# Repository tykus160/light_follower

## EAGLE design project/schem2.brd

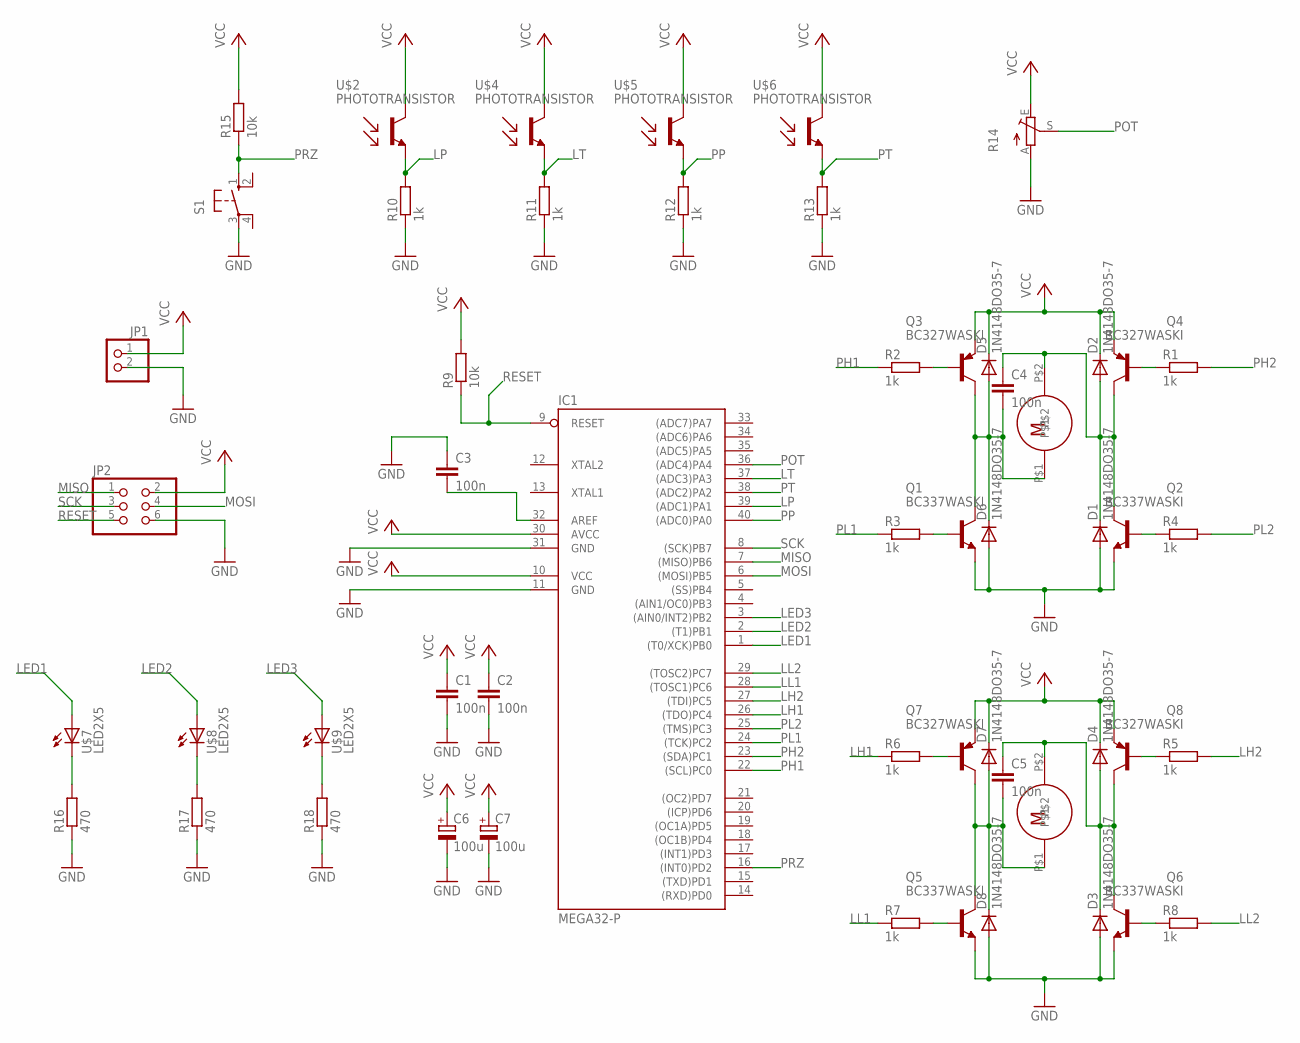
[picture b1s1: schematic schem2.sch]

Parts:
C1, C2, C3, C4, C5: 100n; C025-025X050
C6, C7: 100u; E2-5
D1, D2, D3, D4, D5, D6, D7, D8: 1N4148DO35-7; DO35-7
IC1: MEGA32-P; DIL40
JP1: PINHD-1X2; 1X02
JP2: PINHD-2X3; 2X03
Q1, Q2, Q5, Q6: BC337WASKI; TO92-WASKI
Q3, Q4, Q7, Q8: BC327WASKI; TO92-WASKI
R1, R2, R3, R4, R5, R6, R7, R8, R10, R11, R12, R13: 1k; 0207/7
R9, R15: 10k; 0207/7
R14: TRIM_EU-B64Y; B64Y
R16, R17, R18: 470; 0207/7
S1: 10-XX; B3F-10XX
U$1, U$3: DG02S
U$2, U$4, U$5, U$6: PHOTOTRANSISTOR
U$7, U$8, U$9: LED2X5; LED3MM

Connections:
GND: C1.2, C2.2, C3.1, C6.-, C7.-, D1.A, D3.A, D6.A, D8.A, IC1.11 (GND), IC1.31 (GND), JP1.2, JP2.6, Q1.E, Q2.E, Q5.E, Q6.E, R10.1, R11.1, R12.1, R13.1, R14.A, R16.1, R17.1, R18.1, S1.3
LED1: IC1.1 ((T0/XCK)PB0), U$7.A
LED2: IC1.2 ((T1)PB1), U$8.A
LED3: IC1.3 ((AIN0/INT2)PB2), U$9.A
LH1: IC1.26 ((TDO)PC4), R6.1
LH2: IC1.27 ((TDI)PC5), R5.2
LL1: IC1.28 ((TOSC1)PC6), R7.1
LL2: IC1.29 ((TOSC2)PC7), R8.2
LP: IC1.39 ((ADC1)PA1), R10.2, U$2.E
LT: IC1.37 ((ADC3)PA3), R11.2, U$4.E
MISO: IC1.7 ((MISO)PB6), JP2.1
MOSI: IC1.6 ((MOSI)PB5), JP2.4
unnamed: C4.2, D5.A, D6.C, Q1.C, Q3.C, U$1.P$1
unnamed: C4.1, D1.C, D2.A, Q2.C, Q4.C, U$1.P$2
unnamed: C5.2, D7.A, D8.C, Q5.C, Q7.C, U$3.P$1
unnamed: R16.2, U$7.K (C)
unnamed: Q7.B, R6.2
unnamed: Q8.B, R5.1
unnamed: Q3.B, R2.2
unnamed: Q4.B, R1.1
unnamed: Q2.B, R4.1
unnamed: Q1.B, R3.2
unnamed: Q6.B, R8.1
unnamed: Q5.B, R7.2
unnamed: C5.1, D3.C, D4.A, Q6.C, Q8.C, U$3.P$2
unnamed: C3.2, IC1.32 (AREF)
unnamed: R17.2, U$8.K (C)
unnamed: R18.2, U$9.K (C)
PH1: IC1.22 ((SCL)PC0), R2.1
PH2: IC1.23 ((SDA)PC1), R1.2
PL1: IC1.24 ((TCK)PC2), R3.1
PL2: IC1.25 ((TMS)PC3), R4.2
POT: IC1.36 ((ADC4)PA4), R14.S
PP: IC1.40 ((ADC0)PA0), R12.2, U$5.E
PRZ: IC1.16 ((INT0)PD2), R15.1, S1.1 (S)
PT: IC1.38 ((ADC2)PA2), R13.2, U$6.E
RESET: IC1.9 (RESET), JP2.5, R9.1
SCK: IC1.8 ((SCK)PB7), JP2.3
VCC: C1.1, C2.1, C6.+, C7.+, D2.C, D4.C, D5.C, D7.C, IC1.10 (VCC), IC1.30 (AVCC), JP1.1, JP2.2, Q3.E, Q4.E, Q7.E, Q8.E, R9.2, R14.E, R15.2, U$2.C, U$4.C, U$5.C, U$6.C

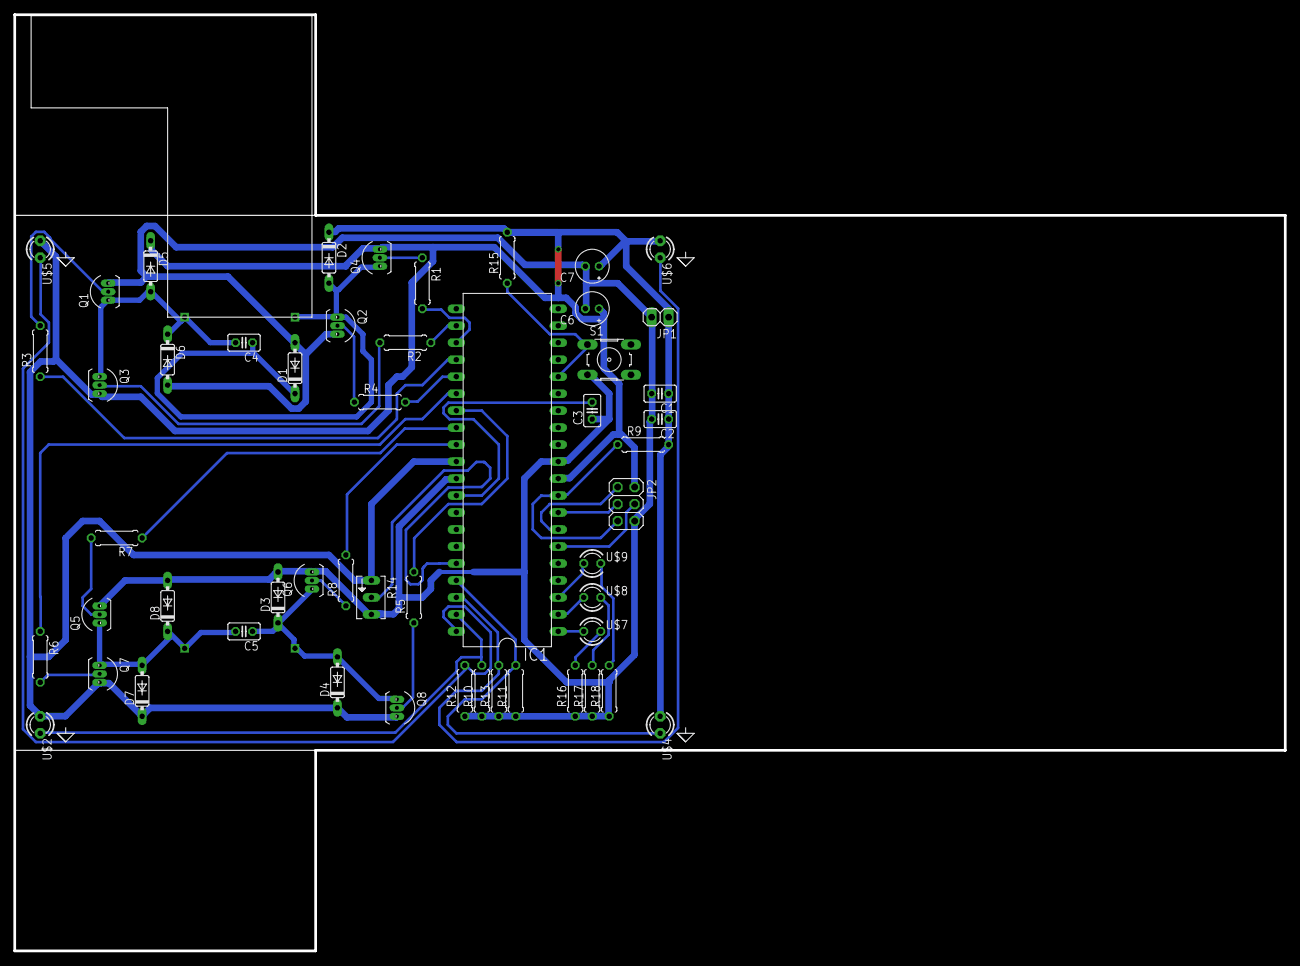
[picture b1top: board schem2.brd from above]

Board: 2 copper layers, 190.0 x 140.0 mm, 54 parts (1 on the bottom side), 39 nets.

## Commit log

2018-04-10 Added old light follower from 2016
